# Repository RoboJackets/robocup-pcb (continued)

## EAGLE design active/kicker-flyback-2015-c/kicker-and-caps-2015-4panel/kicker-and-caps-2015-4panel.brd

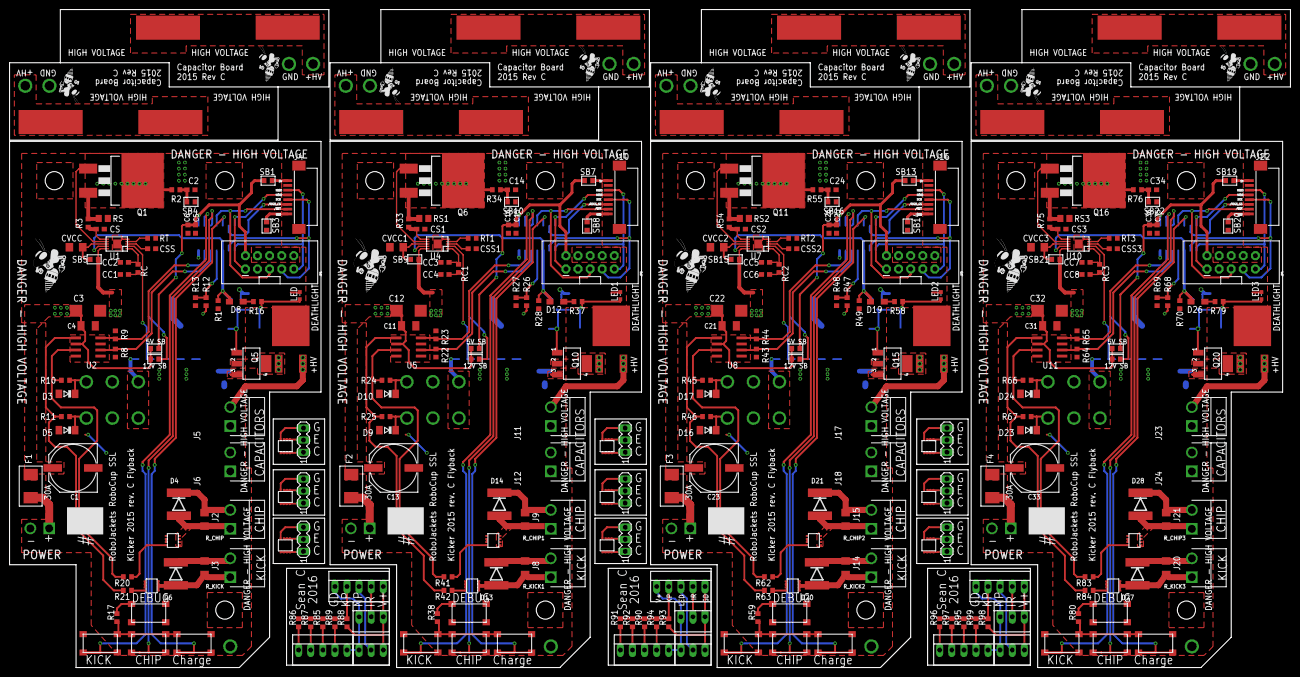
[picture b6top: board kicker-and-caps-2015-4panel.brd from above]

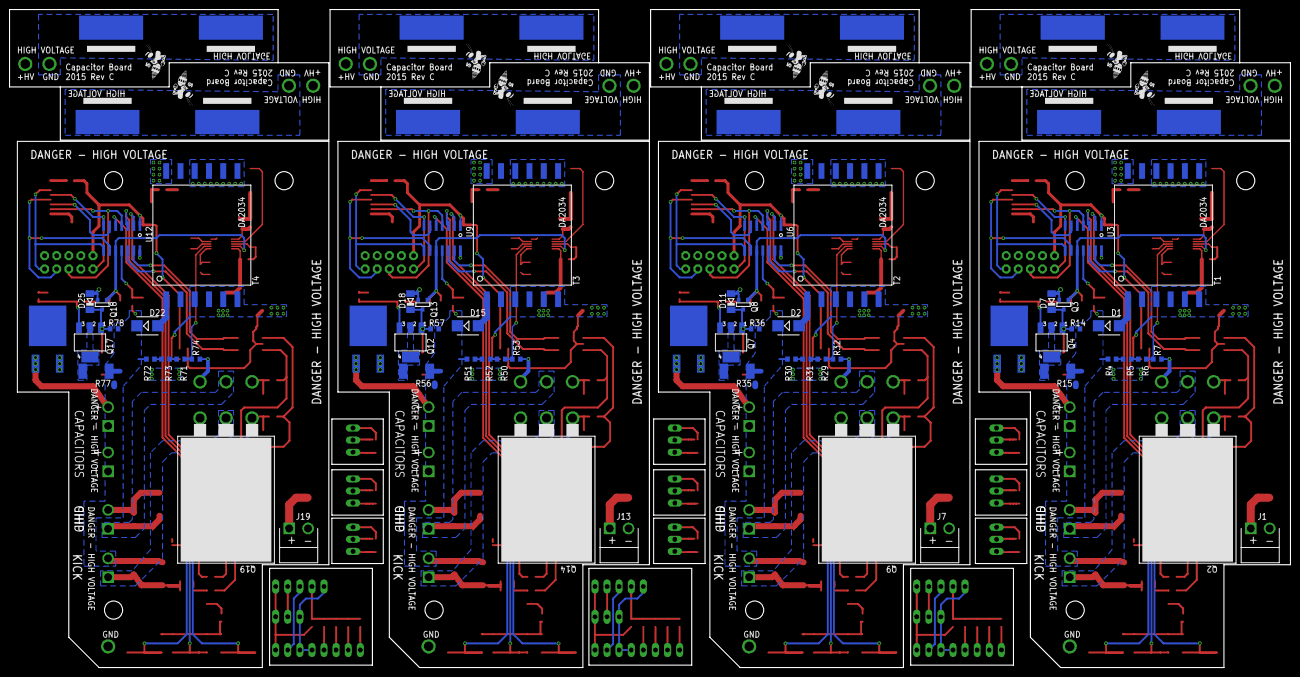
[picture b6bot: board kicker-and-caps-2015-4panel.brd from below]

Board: 2 copper layers, 269.0 x 138.2 mm, 397 parts (68 on the bottom side), 266 nets.

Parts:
C1, C13, C23, C33: UWT1E471MNL1GS; PANASONIC_G
C2, C14, C24, C34: 220pF 100V; C0603
C3, C12, C22, C32: 47uF; C/6032-28R
C4, C11, C21, C31: 4.7uF; C1206K
C5, C15, C25, C35: 47u; C0603K
C6, C16, C26, C36: 4.7u; C0603K
C7, C8, C9, C10, C17, C18, C19, C20, C27, C28, C29, C30, C37, C38, C39, C40: 25MM-DIA_HORIZ
CC1, CC4, CC6, CC8: 22nF; C0603
CC2, CC3, CC5, CC7: 100pF; C0603
CS, CS1, CS2, CS3: 22nF; C0603
CSS, CSS1, CSS2, CSS3: 100nF; C0603
CVCC, CVCC1, CVCC2, CVCC3: 4.7uF, 25v; C1206
D1, D2, D15, D22: STTH3R06U; SMB
D3, D5, D7, D9, D10, D11, D16, D17, D18, D23, D24, D25: BZV55-B18,115; SOD80C
D4, D6, D13, D14, D20, D21, D27, D28: DO-214AB
D8, D12, D19, D26: BAS16H; SOD323-W
F1, F2, F3, F4: 30A; NANO2_157
J1, J7, J13, J19: POWER; JST_VH_2_RA
J2, J9, J15, J21: CHIP; JST_VH_2_RA
J3, J8, J14, J20: KICK; JST_VH_2_RA
J4, J10, J16, J22: 0528520870
J5, J11, J17, J23: Cap 1; JST_VH_2_RA
J6, J12, J18, J24: Cap 2; JST_VH_2_RA
JP1, JP2, JP3, JP4: M05X2SHD_LOCK; 2X5-SHROUDED_LOCK
LED, LED1, LED2, LED3: LTST-S270KRKT; CHIPLED_0603
Q1, Q6, Q11, Q16: STB40NF20; D2PACK
Q2, Q9, Q14, Q19: TO264_2
Q3, Q8, Q13, Q18: FDV303N; SOT-23
Q4, Q5, Q7, Q10, Q12, Q15, Q17, Q20: FQT1N80; SOT223
R1, R8, R9, R22, R23, R28, R43, R44, R49, R64, R65, R70: 10.0k; R0603
R2, R3, R33, R34, R54, R55, R75, R76: 22; R0603
R4, R5, R30, R31, R51, R52, R72, R73: 1.00M, 1% (MCR03EZPFX1004); R0603
R6, R29, R50, R71: 470k 1%; R0603
R7, R32, R53, R74: 16.20k, 1% (MCR03EZPFX1622); R0603
R10, R11, R24, R25, R45, R46, R66, R67: 10; R0603
R12, R26, R47, R68: 1.00M 1%; R0603
R13, R27, R48, R69: 16.2k 1%; R0603
R14, R36, R57, R78: 10M; R0603
R15, R35, R56, R77: RHC2512FT33K0; R2512
R16, R20, R21, R37, R41, R42, R58, R62, R63, R79, R83, R84: 220; R0603
R17, R38, R59, R80: 10K; R0603
R18, R19, R39, R40, R60, R61, R81, R82: PWR163S-25-3301J
R85, R86, R87, R88, R89, R90, R91, R92, R93, R94, R95, R96, R97, R98, R99: R0603
RC, RC1, RC2, RC3: 6.8k; R0603
RS, RS1, RS2, RS3: 0.015 (ERJ-6BWFR015V); R0805
RT, RT1, RT2, RT3: 140k; R0603
R_CHIP, R_CHIP1, R_CHIP2, R_CHIP3: NP; R1206
R_KICK, R_KICK1, R_KICK2, R_KICK3: NP; R1206
SB1, SB2, SB7, SB11, SB13, SB17, SB19, SB23: 5V_SEL; SB0603
SB3, SB8, SB14, SB20: GND_NC; SB0603
SB4, SB5, SB9, SB10, SB15, SB16, SB21, SB22: NO; SB0603
SB6, SB12, SB18, SB24: 12V Se; SB0603
SV1, SV2, SV3, SV4, SV5, SV6, SV7, SV8, SV9: MA03-1
T1, T2, T3, T4: DA2034
TP1, TP2, TP3, TP4: GND; VIA_2MM
U1, U4, U7, U10: LT3757; MSOP-10-MSE
U2, U5, U8, U11: IX4427N; SOIC-8
U3, U6, U9, U12: ATTINY441/841SSU/SSUR; SOIC-14
U$1, U$16, U$31, U$46: ROBOBUZZ_0.6X
U$2, U$3, U$4, U$5, U$17, U$18, U$19, U$20, U$32, U$33, U$34, U$35, U$47, U$48, U$49, U$50: PTS645SK50SMTR92
U$6, U$7, U$21, U$22, U$36, U$37, U$51, U$52, U$61, U$62, U$63, U$64, U$65, U$66, U$67, U$68, U$69: TIG058E8-TL-H; ECH8
U$8, U$9, U$12, U$13, U$23, U$24, U$27, U$28, U$38, U$39, U$42, U$43, U$53, U$54, U$57, U$58: VIA_2MM
U$10, U$11, U$14, U$15, U$25, U$26, U$29, U$30, U$40, U$41, U$44, U$45, U$55, U$56, U$59, U$60: ROBOBUZZ_0.4X
X1, X2, X5, X6, X9, X10: 22-23-2031
X3, X4, X7, X8, X11, X12: 22-23-2051

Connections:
5V: J4.8, SB1.1
5V1: J10.8, SB7.1
5V2: J16.8, SB13.1
5V3: J22.8, SB19.1
+12V: C1.+, F1.P$2, SB5.1, SB6.2, T1.3, T1.4, T1.5, T1.6, U1.10
+12V1: C13.+, F2.P$2, SB9.1, SB12.2, T2.3, T2.4, T2.5, T2.6, U4.10
+12V2: C23.+, F3.P$2, SB15.1, SB18.2, T3.3, T3.4, T3.5, T3.6, U7.10
+12V3: C33.+, F4.P$2, SB21.1, SB24.2, T4.3, T4.4, T4.5, T4.6, U10.10
/KICK_CS: J4.3, U3.6
/KICK_CS1: J10.3, U6.6
/KICK_CS2: J16.3, U9.6
/KICK_CS3: J22.3, U12.6
/RST: J4.2, JP1.5, U3.4
/RST1: J10.2, JP2.5, U6.4
/RST2: J16.2, JP3.5, U9.4
/RST3: J22.2, JP4.5, U12.4
C: SV1.1, U$61.P5, U$61.P6, U$61.P7, U$61.P8
C1: SV2.1, U$62.P5, U$62.P6, U$62.P7, U$62.P8
C2: SV3.1, U$63.P5, U$63.P6, U$63.P7, U$63.P8
C3: SV4.1, U$64.P5, U$64.P6, U$64.P7, U$64.P8
C4: SV5.1, U$65.P5, U$65.P6, U$65.P7, U$65.P8
C5: SV6.1, U$66.P5, U$66.P6, U$66.P7, U$66.P8
C6: SV7.1, U$67.P5, U$67.P6, U$67.P7, U$67.P8
C7: SV8.1, U$68.P5, U$68.P6, U$68.P7, U$68.P8
C8: SV9.1, U$69.P5, U$69.P6, U$69.P7, U$69.P8
CHARGE: D8.A, Q3.3, R1.2, U1.9, U3.10
CHARGE1: D12.A, Q8.3, R28.2, U4.9, U6.10
CHARGE2: D19.A, Q13.3, R49.2, U7.9, U9.10
CHARGE3: D26.A, Q18.3, R70.2, U10.9, U12.10
CHIP: R8.2, U2.2, U3.12
CHIP1: R22.2, U5.2, U6.12
CHIP2: R43.2, U8.2, U9.12
CHIP3: R64.2, U11.2, U12.12
DB_CHG: U3.5, U$4.1, U$4.2
DB_CHG1: U6.5, U$19.1, U$19.2
DB_CHG2: U9.5, U$34.1, U$34.2
DB_CHG3: U12.5, U$49.1, U$49.2
DB_CHIP: U3.3, U$3.1, U$3.2
DB_CHIP1: U6.3, U$18.1, U$18.2
DB_CHIP2: U9.3, U$33.1, U$33.2
DB_CHIP3: U12.3, U$48.1, U$48.2
DB_KICK: U3.2, U$5.1, U$5.2
DB_KICK1: U6.2, U$20.1, U$20.2
DB_KICK2: U9.2, U$35.1, U$35.2
DB_KICK3: U12.2, U$50.1, U$50.2
E: SV1.2, U$61.P1, U$61.P2, U$61.P3
E1: SV2.2, U$62.P1, U$62.P2, U$62.P3
E2: SV3.2, U$63.P1, U$63.P2, U$63.P3
E3: SV4.2, U$64.P1, U$64.P2, U$64.P3
E4: SV5.2, U$65.P1, U$65.P2, U$65.P3
E5: SV6.2, U$66.P1, U$66.P2, U$66.P3
E6: SV7.2, U$67.P1, U$67.P2, U$67.P3
E7: SV8.2, U$68.P1, U$68.P2, U$68.P3
E8: SV9.2, U$69.P1, U$69.P2, U$69.P3
G: SV1.3, U$61.P4
G1: SV2.3, U$62.P4
G2: SV3.3, U$63.P4
G3: SV4.3, U$64.P4
G4: SV5.3, U$65.P4
G5: SV6.3, U$66.P4
G6: SV7.3, U$67.P4
G7: SV8.3, U$68.P4
G8: SV9.3, U$69.P4
GATE_C: R20.1, U$6.P4
GATE_C1: R41.1, U$21.P4
GATE_C2: R62.1, U$36.P4
GATE_C3: R83.1, U$51.P4
GATE_K: R21.1, U$7.P4
GATE_K1: R42.1, U$22.P4
GATE_K2: R63.1, U$37.P4
GATE_K3: R84.1, U$52.P4
GND: C1.-, C2.2, C3.-, C4.2, C5.2, C6.2, CC1.2, CC2.2, CS.2, CSS.2, CVCC.2, D3.A, D5.A, D7.A, J1.2, J5.1, J6.1, JP1.4, JP1.6, JP1.8, JP1.10, LED.C, Q2.E_BOT, Q2.E_TOP, Q3.2, Q5.3, R1.1, R7.1, R8.1, R9.1, R13.1, RS.1, RT.2, SB3.1, SB4.2, T1.12, TP1.P$1, U1.5, U1.11, U2.3, U3.14, U$2.3, U$2.4, U$6.P1, U$6.P2, U$6.P3, U$7.P1, U$7.P2, U$7.P3
GND1: C7.-, C8.-, U$9.P$1
GND2: C9.-, C10.-, U$13.P$1
GND3: C11.2, C12.-, C13.-, C14.2, C15.2, C16.2, CC3.2, CC4.2, CS1.2, CSS1.2, CVCC1.2, D9.A, D10.A, D11.A, J7.2, J11.1, J12.1, JP2.4, JP2.6, JP2.8, JP2.10, LED1.C, Q8.2, Q9.E_BOT, Q9.E_TOP, Q10.3, R22.1, R23.1, R27.1, R28.1, R32.1, RS1.1, RT1.2, SB8.1, SB10.2, T2.12, TP2.P$1, U4.5, U4.11, U5.3, U6.14, U$17.3, U$17.4, U$21.P1, U$21.P2, U$21.P3, U$22.P1, U$22.P2, U$22.P3
GND4: C17.-, C18.-, U$24.P$1
GND5: C19.-, C20.-, U$28.P$1
GND6: C21.2, C22.-, C23.-, C24.2, C25.2, C26.2, CC5.2, CC6.2, CS2.2, CSS2.2, CVCC2.2, D16.A, D17.A, D18.A, J13.2, J17.1, J18.1, JP3.4, JP3.6, JP3.8, JP3.10, LED2.C, Q13.2, Q14.E_BOT, Q14.E_TOP, Q15.3, R43.1, R44.1, R48.1, R49.1, R53.1, RS2.1, RT2.2, SB14.1, SB16.2, T3.12, TP3.P$1, U7.5, U7.11, U8.3, U9.14, U$32.3, U$32.4, U$36.P1, U$36.P2, U$36.P3, U$37.P1, U$37.P2, U$37.P3
GND7: C27.-, C28.-, U$39.P$1
GND8: C29.-, C30.-, U$43.P$1
GND9: C31.2, C32.-, C33.-, C34.2, C35.2, C36.2, CC7.2, CC8.2, CS3.2, CSS3.2, CVCC3.2, D23.A, D24.A, D25.A, J19.2, J23.1, J24.1, JP4.4, JP4.6, JP4.8, JP4.10, LED3.C, Q18.2, Q19.E_BOT, Q19.E_TOP, Q20.3, R64.1, R65.1, R69.1, R70.1, R74.1, RS3.1, RT3.2, SB20.1, SB22.2, T4.12, TP4.P$1, U10.5, U10.11, U11.3, U12.14, U$47.3, U$47.4, U$51.P1, U$51.P2, U$51.P3, U$52.P1, U$52.P2, U$52.P3
GND10: C37.-, C38.-, U$54.P$1
GND11: C39.-, C40.-, U$58.P$1
GND12: R88.1, X1.3, X2.3, X4.5
GND13: R93.1, X5.3, X6.3, X8.5
GND14: R98.1, X9.3, X10.3, X12.5
HV: D1.C, D4.C, D6.C, J2.2, J3.2, J5.2, J6.2, R4.2, R12.2, R14.2, R15.2, R18.P$3, R19.P$2, R_CHIP.2, R_KICK.2
HV1: C7.+, C8.+, U$8.P$1
HV2: C9.+, C10.+, U$12.P$1
HV3: D2.C, D13.C, D14.C, J8.2, J9.2, J11.2, J12.2, R26.2, R30.2, R35.2, R36.2, R39.P$3, R40.P$2, R_CHIP1.2, R_KICK1.2
HV4: C17.+, C18.+, U$23.P$1
HV5: C19.+, C20.+, U$27.P$1
HV6: D15.C, D20.C, D21.C, J14.2, J15.2, J17.2, J18.2, R47.2, R51.2, R56.2, R57.2, R60.P$3, R61.P$2, R_CHIP2.2, R_KICK2.2
HV7: C27.+, C28.+, U$38.P$1
HV8: C29.+, C30.+, U$42.P$1
HV9: D22.C, D27.C, D28.C, J20.2, J21.2, J23.2, J24.2, R68.2, R72.2, R77.2, R78.2, R81.P$3, R82.P$2, R_CHIP3.2, R_KICK3.2
HV10: C37.+, C38.+, U$53.P$1
HV11: C39.+, C40.+, U$57.P$1
IR: X2.2, X4.4
IR1: X6.2, X8.4
IR2: X10.2, X12.4
KEYPAD: R85.2, R86.2, R87.2, R88.2, R89.2, X4.2
KEYPAD1: R90.2, R91.2, R92.2, R93.2, R94.2, X8.2
KEYPAD2: R95.2, R96.2, R97.2, R98.2, R99.2, X12.2
KICK: R9.2, U2.4, U3.13
KICK1: R23.2, U5.4, U6.13
KICK2: R44.2, U8.4, U9.13
KICK3: R65.2, U11.4, U12.13
LED: X1.2, X4.3
LED1: X5.2, X8.3
LED2: X9.2, X12.3
MISO: J4.6, JP1.9, U3.8
MISO1: J10.6, JP2.9, U6.8
MISO2: J16.6, JP3.9, U9.8
MISO3: J22.6, JP4.9, U12.8
MOSI: J4.5, JP1.1, U3.7
MOSI1: J10.5, JP2.1, U6.7
MOSI2: J16.5, JP3.1, U9.7
MOSI3: J22.5, JP4.1, U12.7
unnamed: D3.C, Q2.G_TOP, R10.2
unnamed: Q1.1, U1.7
unnamed: J4.1, SB3.2
unnamed: CC2.1, RC.1, U1.1
unnamed: CC1.1, RC.2
unnamed: R11.1, R21.2, U2.5
unnamed: R4.1, R5.2
unnamed: D5.C, Q2.G_BOT, R11.2
unnamed: R5.1, R6.2
unnamed: D6.A, J3.1, Q2.C_BOT, R_KICK.1, U$7.P5, U$7.P6, U$7.P7, U$7.P8
unnamed: D4.A, J2.1, Q2.C_TOP, R_CHIP.1, U$6.P5, U$6.P6, U$6.P7, U$6.P8
unnamed: R17.2, U$2.1, U$2.2
unnamed: Q6.1, U4.7
unnamed: C3.+, C4.1, SB2.1, SB6.1, U2.6
unnamed: R10.1, R20.2, U2.7
unnamed: R17.1, U$3.3, U$3.4, U$4.3, U$4.4, U$5.3, U$5.4
unnamed: F2.P$1, J7.1
unnamed: R24.1, R41.2, U5.7
unnamed: Q5.2, Q5.4, R18.P$2, R19.P$3
unnamed: D7.C, Q3.1, Q4.1, Q5.1, R14.1
unnamed: Q4.2, Q4.4, R15.1
unnamed: D9.C, Q9.G_BOT, R25.2
unnamed: CC3.1, RC1.1, U4.1
unnamed: F1.P$1, J1.1
unnamed: CSS1.1, U4.3
unnamed: CSS.1, U1.3
unnamed: RT.1, U1.4
unnamed: CVCC.1, SB5.2, U1.8
unnamed: LED.A, Q4.3, R16.2
unnamed: CS.1, R3.1, U1.6
unnamed: C2.1, R2.1, SB4.1
unnamed: D8.C, R16.1
unnamed: RT1.1, U4.4
unnamed: CC4.1, RC1.2
unnamed: CVCC1.1, SB9.2, U4.8
unnamed: J10.1, SB8.2
unnamed: CS1.1, R33.1, U4.6
unnamed: C14.1, R34.1, SB10.1
unnamed: D11.C, Q7.1, Q8.1, Q10.1, R36.1
unnamed: LED1.A, Q7.3, R37.2
unnamed: D12.C, R37.1
unnamed: Q7.2, Q7.4, R35.1
unnamed: D14.A, J9.1, Q9.C_TOP, R_CHIP1.1, U$21.P5, U$21.P6, U$21.P7, U$21.P8
unnamed: D10.C, Q9.G_TOP, R24.2
unnamed: Q1.2, R2.2, T1.7, T1.8, T1.9, T1.10
unnamed: Q6.2, R34.2, T2.7, T2.8, T2.9, T2.10
unnamed: D2.A, T2.1
unnamed: D1.A, T1.1
unnamed: R25.1, R42.2, U5.5
unnamed: D13.A, J8.1, Q9.C_BOT, R_KICK1.1, U$22.P5, U$22.P6, U$22.P7, U$22.P8
unnamed: R30.1, R31.2
unnamed: R29.2, R31.1
unnamed: R38.1, U$18.3, U$18.4, U$19.3, U$19.4, U$20.3, U$20.4
unnamed: R38.2, U$17.1, U$17.2
unnamed: Q10.2, Q10.4, R39.P$2, R40.P$3
unnamed: C11.1, C12.+, SB11.1, SB12.1, U5.6
unnamed: Q11.1, U7.7
unnamed: F3.P$1, J13.1
unnamed: R45.1, R62.2, U8.7
unnamed: D16.C, Q14.G_BOT, R46.2
unnamed: CC5.1, RC2.1, U7.1
unnamed: CSS2.1, U7.3
unnamed: RT2.1, U7.4
unnamed: CC6.1, RC2.2
unnamed: CVCC2.1, SB15.2, U7.8
unnamed: J16.1, SB14.2
unnamed: CS2.1, R54.1, U7.6
unnamed: C24.1, R55.1, SB16.1
unnamed: D18.C, Q12.1, Q13.1, Q15.1, R57.1
unnamed: LED2.A, Q12.3, R58.2
unnamed: D19.C, R58.1
unnamed: Q12.2, Q12.4, R56.1
unnamed: D21.A, J15.1, Q14.C_TOP, R_CHIP2.1, U$36.P5, U$36.P6, U$36.P7, U$36.P8
unnamed: D17.C, Q14.G_TOP, R45.2
unnamed: Q11.2, R55.2, T3.7, T3.8, T3.9, T3.10
unnamed: D15.A, T3.1
unnamed: R46.1, R63.2, U8.5
unnamed: D20.A, J14.1, Q14.C_BOT, R_KICK2.1, U$37.P5, U$37.P6, U$37.P7, U$37.P8
unnamed: R51.1, R52.2
unnamed: R50.2, R52.1
unnamed: R59.1, U$33.3, U$33.4, U$34.3, U$34.4, U$35.3, U$35.4
unnamed: R59.2, U$32.1, U$32.2
unnamed: Q15.2, Q15.4, R60.P$2, R61.P$3
unnamed: C21.1, C22.+, SB17.1, SB18.1, U8.6
unnamed: Q16.1, U10.7
unnamed: F4.P$1, J19.1
unnamed: R66.1, R83.2, U11.7
unnamed: D23.C, Q19.G_BOT, R67.2
unnamed: CC7.1, RC3.1, U10.1
unnamed: CSS3.1, U10.3
unnamed: RT3.1, U10.4
unnamed: CC8.1, RC3.2
unnamed: CVCC3.1, SB21.2, U10.8
unnamed: J22.1, SB20.2
unnamed: CS3.1, R75.1, U10.6
unnamed: C34.1, R76.1, SB22.1
unnamed: D25.C, Q17.1, Q18.1, Q20.1, R78.1
unnamed: LED3.A, Q17.3, R79.2
unnamed: D26.C, R79.1
unnamed: Q17.2, Q17.4, R77.1
unnamed: D28.A, J21.1, Q19.C_TOP, R_CHIP3.1, U$51.P5, U$51.P6, U$51.P7, U$51.P8
unnamed: D24.C, Q19.G_TOP, R66.2
unnamed: Q16.2, R76.2, T4.7, T4.8, T4.9, T4.10
unnamed: D22.A, T4.1
unnamed: R67.1, R84.2, U11.5
unnamed: D27.A, J20.1, Q19.C_BOT, R_KICK3.1, U$52.P5, U$52.P6, U$52.P7, U$52.P8
unnamed: R72.1, R73.2
unnamed: R71.2, R73.1
unnamed: R80.1, U$48.3, U$48.4, U$49.3, U$49.4, U$50.3, U$50.4
unnamed: R80.2, U$47.1, U$47.2
unnamed: Q20.2, Q20.4, R81.P$2, R82.P$3
unnamed: C31.1, C32.+, SB23.1, SB24.1, U11.6
unnamed: R89.1, X3.4
unnamed: R85.1, X3.3
unnamed: R87.1, X3.2
unnamed: R86.1, X3.1
unnamed: R94.1, X7.4
unnamed: R90.1, X7.3
unnamed: R92.1, X7.2
unnamed: R91.1, X7.1
unnamed: R99.1, X11.4
unnamed: R95.1, X11.3
unnamed: R97.1, X11.2
unnamed: R96.1, X11.1
NAG: Q1.3, R3.2, RS.2
NAG1: Q6.3, R33.2, RS1.2
NAG2: Q11.3, R54.2, RS2.2
NAG3: Q16.3, R75.2, RS3.2
SCK: J4.4, JP1.7, U3.9
SCK1: J10.4, JP2.7, U6.9
SCK2: J16.4, JP3.7, U9.9
SCK3: J22.4, JP4.7, U12.9
VCC: X1.1, X2.1, X3.5, X4.1
VCC1: X5.1, X6.1, X7.5, X8.1
VCC2: X9.1, X10.1, X11.5, X12.1
VDD: C5.1, C6.1, JP1.2, SB1.2, SB2.2, U3.1
VDD1: C15.1, C16.1, JP2.2, SB7.2, SB11.2, U6.1
VDD2: C25.1, C26.1, JP3.2, SB13.2, SB17.2, U9.1
VDD3: C35.1, C36.1, JP4.2, SB19.2, SB23.2, U12.1
VFB: R6.1, R7.2, U1.2
VFB1: R29.1, R32.2, U4.2
VFB2: R50.1, R53.2, U7.2
VFB3: R71.1, R74.2, U10.2
V_MONITOR: R12.1, R13.2, U3.11
V_MONITOR1: R26.1, R27.2, U6.11
V_MONITOR2: R47.1, R48.2, U9.11
V_MONITOR3: R68.1, R69.2, U12.11

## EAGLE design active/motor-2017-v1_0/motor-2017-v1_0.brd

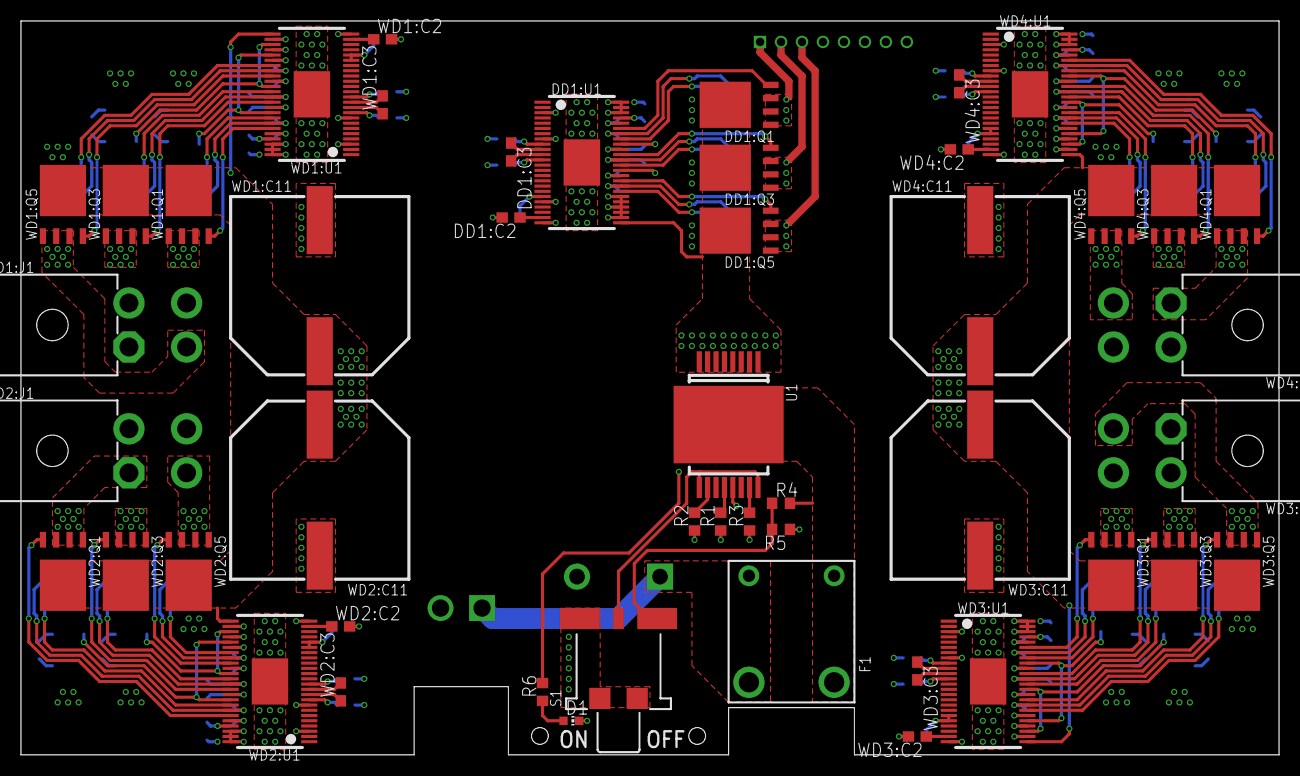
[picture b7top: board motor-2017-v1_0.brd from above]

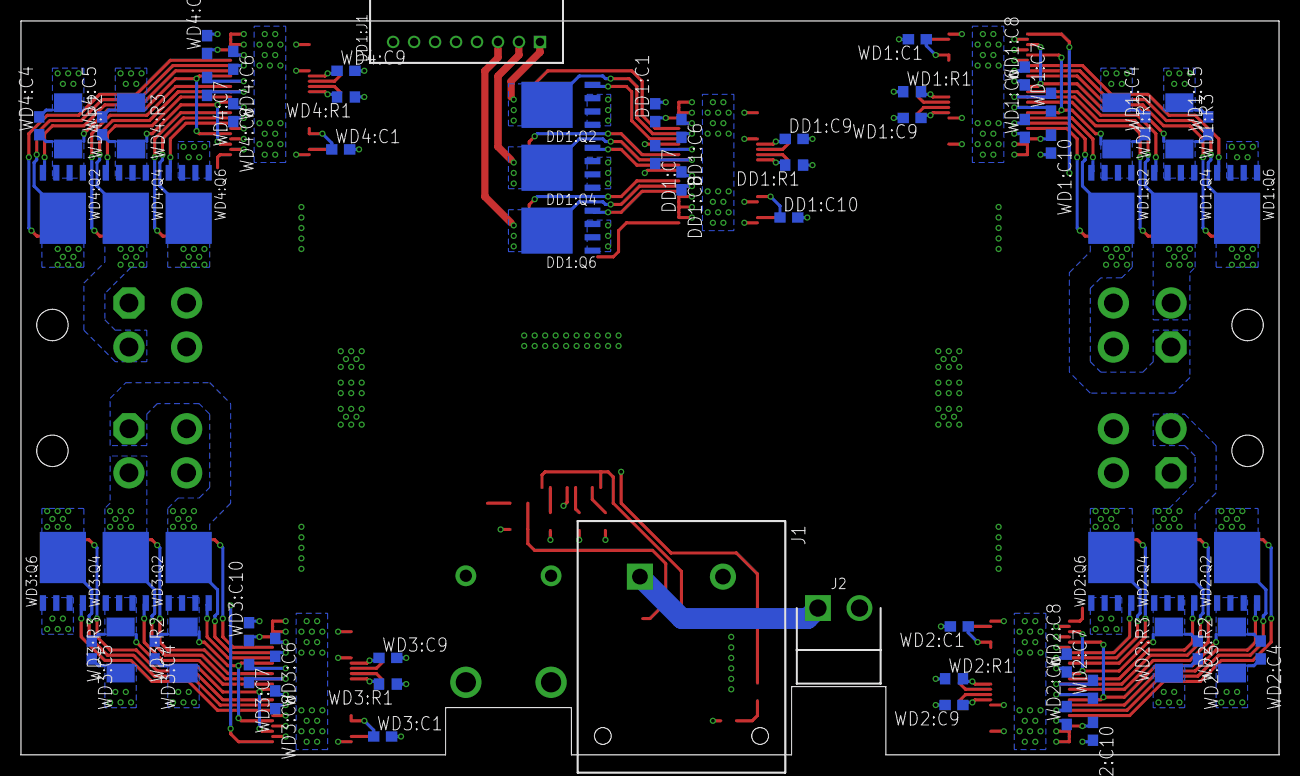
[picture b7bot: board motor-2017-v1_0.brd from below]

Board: 4 copper layers, 120.0 x 70.0 mm, 117 parts (69 on the bottom side), 104 nets.

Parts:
D1: Green; CHIP-LED0603
DD1:C1, DD1:C2: 1uF; C0603
DD1:C3: 22000pF 50V; C0603
DD1:C6, DD1:C7, DD1:C8, DD1:C10: 0.1uF 50V; C0603
DD1:C9: 2.2uF 50V; C0603
DD1:J1: 8-PIN_2MM-H; 2MM-8-H
DD1:Q1, DD1:Q2, DD1:Q3, DD1:Q4, DD1:Q5, DD1:Q6: IRFH7545; PQFN_5X6_E
DD1:R1: 10k; R0603
DD1:U1: DRV8303DCA; TSSOP-48_PAD
F1: 30A; FUSEHOLDER_3549_X2
J1: DF22-2; DF22-2-H
J2: B2PS-CENTERED-VH(LF)(SN); B2PS-CENTERED
R1: 10k; R0603
R2, R3, R6: 1k; R0603
R4: 270k; R0603
R5: 100k; R0603
S1: 34EWMSP12MRT; 34EWMSP12M6RT
U1: VND5E006ASPTR-E; POWERSO-16
WD1:C1, WD1:C2, WD2:C1, WD2:C2, WD3:C1, WD3:C2, WD4:C1, WD4:C2: 1uF; C0603
WD1:C3, WD2:C3, WD3:C3, WD4:C3: 22000pF 50V; C0603
WD1:C4, WD1:C5, WD2:C4, WD2:C5, WD3:C4, WD3:C5, WD4:C4, WD4:C5: 10000pF 50V; C0603
WD1:C6, WD1:C7, WD1:C8, WD1:C10, WD2:C6, WD2:C7, WD2:C8, WD2:C10, WD3:C6, WD3:C7, WD3:C8, WD3:C10, WD4:C6, WD4:C7, WD4:C8, WD4:C10: 0.1uF 50V; C0603
WD1:C9, WD2:C9, WD3:C9, WD4:C9: 2.2uF 50V; C0603
WD1:C11, WD2:C11, WD3:C11, WD4:C11: EEE-FK1H102AM; PANASONIC_J16
WD1:J1, WD2:J1, WD3:J1, WD4:J1: MINIFITJR_HDR_2X2; 0039301040
WD1:Q1, WD1:Q2, WD1:Q3, WD1:Q4, WD1:Q5, WD1:Q6, WD2:Q1, WD2:Q2, WD2:Q3, WD2:Q4, WD2:Q5, WD2:Q6, WD3:Q1, WD3:Q2, WD3:Q3, WD3:Q4, WD3:Q5, WD3:Q6, WD4:Q1, WD4:Q2, WD4:Q3, WD4:Q4, WD4:Q5, WD4:Q6: IRFH7545; PQFN_5X6_E
WD1:R1, WD2:R1, WD3:R1, WD4:R1: 10k; R0603
WD1:R2, WD1:R3, WD2:R2, WD2:R3, WD3:R2, WD3:R3, WD4:R2, WD4:R3: ERJ-MB1SF1M0U; R2010
WD1:U1, WD2:U1, WD3:U1, WD4:U1: DRV8303DCA; TSSOP-48_PAD

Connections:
+3.3V: DD1:C1.1, DD1:C10.1, DD1:J1.7, DD1:R1.1, DD1:U1.19, DD1:U1.45, WD1:C1.1, WD1:C10.1, WD1:R1.1, WD1:U1.19, WD1:U1.20, WD1:U1.45, WD2:C1.1, WD2:C10.1, WD2:R1.1, WD2:U1.19, WD2:U1.20, WD2:U1.45, WD3:C1.1, WD3:C10.1, WD3:R1.1, WD3:U1.19, WD3:U1.20, WD3:U1.45, WD4:C1.1, WD4:C10.1, WD4:R1.1, WD4:U1.19, WD4:U1.20, WD4:U1.45
+18.5V: DD1:Q1.5678, DD1:Q3.5678, DD1:Q5.5678, DD1:U1.25, R6.2, U1.1, U1.2, U1.3, U1.4, U1.5, U1.6, U1.7, U1.8, WD1:C11.+, WD1:Q1.5678, WD1:Q3.5678, WD1:Q5.5678, WD1:U1.25, WD2:C11.+, WD2:Q1.5678, WD2:Q3.5678, WD2:Q5.5678, WD2:U1.25, WD3:C11.+, WD3:Q1.5678, WD3:Q3.5678, WD3:Q5.5678, WD3:U1.25, WD4:C11.+, WD4:Q1.5678, WD4:Q3.5678, WD4:Q5.5678, WD4:U1.25
DD1:N$1: DD1:C2.1, DD1:U1.23
DD1:N$2: DD1:C3.1, DD1:U1.10
DD1:N$3: DD1:C3.2, DD1:U1.11
DD1:N$4: DD1:C9.1, DD1:U1.9
DD1:N$6: DD1:Q2.4, DD1:U1.41
DD1:N$8: DD1:Q1.4, DD1:U1.43
DD1:N$10: DD1:Q4.4, DD1:U1.36
DD1:N$12: DD1:Q3.4, DD1:U1.38
DD1:N$13: DD1:C6.1, DD1:U1.44
DD1:N$14: DD1:C7.1, DD1:U1.39
DD1:N$16: DD1:Q6.4, DD1:U1.31
DD1:N$17: DD1:Q5.4, DD1:U1.33
DD1:N$18: DD1:C8.1, DD1:U1.34
DD1:N$19: DD1:R1.2, DD1:U1.12
DD1:PHASE_A: DD1:C6.2, DD1:J1.1, DD1:Q1.1, DD1:Q1.2, DD1:Q1.3, DD1:Q2.5678, DD1:U1.42
DD1:PHASE_B: DD1:C7.2, DD1:J1.2, DD1:Q3.1, DD1:Q3.2, DD1:Q3.3, DD1:Q4.5678, DD1:U1.37
DD1:PHASE_C: DD1:C8.2, DD1:J1.3, DD1:Q5.1, DD1:Q5.2, DD1:Q5.3, DD1:Q6.5678, DD1:U1.32
GND: D1.C, DD1:C1.2, DD1:C2.2, DD1:C9.2, DD1:C10.2, DD1:J1.8, DD1:Q2.1, DD1:Q2.2, DD1:Q2.3, DD1:Q4.1, DD1:Q4.2, DD1:Q4.3, DD1:Q6.1, DD1:Q6.2, DD1:Q6.3, DD1:U1.3, DD1:U1.8, DD1:U1.20, DD1:U1.24, DD1:U1.26, DD1:U1.27, DD1:U1.28, DD1:U1.29, DD1:U1.30, DD1:U1.35, DD1:U1.40, DD1:U1.46, DD1:U1.47, DD1:U1.48, DD1:U1.PAD, J1.2, J2.2, R1.1, R2.1, R3.1, R5.1, S1.3, S1.LEG1, S1.LEG3, U1.13, WD1:C1.2, WD1:C2.2, WD1:C4.2, WD1:C5.2, WD1:C9.2, WD1:C10.2, WD1:C11.-, WD1:Q6.1, WD1:Q6.2, WD1:Q6.3, WD1:R2.1, WD1:R3.1, WD1:U1.3, WD1:U1.8, WD1:U1.24, WD1:U1.26, WD1:U1.28, WD1:U1.30, WD1:U1.46, WD1:U1.47, WD1:U1.48, WD1:U1.PAD, WD2:C1.2, WD2:C2.2, WD2:C4.2, WD2:C5.2, WD2:C9.2, WD2:C10.2, WD2:C11.-, WD2:Q6.1, WD2:Q6.2, WD2:Q6.3, WD2:R2.1, WD2:R3.1, WD2:U1.3, WD2:U1.8, WD2:U1.24, WD2:U1.26, WD2:U1.28, WD2:U1.30, WD2:U1.46, WD2:U1.47, WD2:U1.48, WD2:U1.PAD, WD3:C1.2, WD3:C2.2, WD3:C4.2, WD3:C5.2, WD3:C9.2, WD3:C10.2, WD3:C11.-, WD3:Q6.1, WD3:Q6.2, WD3:Q6.3, WD3:R2.1, WD3:R3.1, WD3:U1.3, WD3:U1.8, WD3:U1.24, WD3:U1.26, WD3:U1.28, WD3:U1.30, WD3:U1.46, WD3:U1.47, WD3:U1.48, WD3:U1.PAD, WD4:C1.2, WD4:C2.2, WD4:C4.2, WD4:C5.2, WD4:C9.2, WD4:C10.2, WD4:C11.-, WD4:Q6.1, WD4:Q6.2, WD4:Q6.3, WD4:R2.1, WD4:R3.1, WD4:U1.3, WD4:U1.8, WD4:U1.24, WD4:U1.26, WD4:U1.28, WD4:U1.30, WD4:U1.46, WD4:U1.47, WD4:U1.48, WD4:U1.PAD
unnamed: R3.2, U1.15
unnamed: R2.2, U1.10
unnamed: R1.2, U1.12
unnamed: R4.1, R5.2, S1.1
unnamed: S1.2, U1.9, U1.16
unnamed: D1.A, R6.1
VBATT: F1.2, F1.LEG2, R4.2, U1.17
VIN: F1.1, F1.LEG1, J1.1, J2.1
WD1:N$1: WD1:C2.1, WD1:U1.23
WD1:N$2: WD1:C3.1, WD1:U1.10
WD1:N$3: WD1:C3.2, WD1:U1.11
WD1:N$4: WD1:C9.1, WD1:U1.9
WD1:N$6: WD1:Q2.4, WD1:U1.41
WD1:N$8: WD1:Q1.4, WD1:U1.43
WD1:N$10: WD1:Q4.4, WD1:U1.36
WD1:N$12: WD1:Q3.4, WD1:U1.38
WD1:N$13: WD1:C6.1, WD1:U1.44
WD1:N$14: WD1:C7.1, WD1:U1.39
WD1:N$16: WD1:Q6.4, WD1:U1.31
WD1:N$17: WD1:Q5.4, WD1:U1.33
WD1:N$18: WD1:C8.1, WD1:U1.34
WD1:N$19: WD1:R1.2, WD1:U1.12
WD1:PHASE_A: WD1:C6.2, WD1:J1.1, WD1:Q1.1, WD1:Q1.2, WD1:Q1.3, WD1:Q2.5678, WD1:U1.42
WD1:PHASE_B: WD1:C7.2, WD1:J1.2, WD1:Q3.1, WD1:Q3.2, WD1:Q3.3, WD1:Q4.5678, WD1:U1.37
WD1:PHASE_C: WD1:C8.2, WD1:J1.3, WD1:Q5.1, WD1:Q5.2, WD1:Q5.3, WD1:Q6.5678, WD1:U1.32
WD1:S1: WD1:C4.1, WD1:Q2.1, WD1:Q2.2, WD1:Q2.3, WD1:R2.2, WD1:U1.29, WD1:U1.40
WD1:S2: WD1:C5.1, WD1:Q4.1, WD1:Q4.2, WD1:Q4.3, WD1:R3.2, WD1:U1.27, WD1:U1.35
WD2:N$1: WD2:C2.1, WD2:U1.23
WD2:N$2: WD2:C3.1, WD2:U1.10
WD2:N$3: WD2:C3.2, WD2:U1.11
WD2:N$4: WD2:C9.1, WD2:U1.9
WD2:N$6: WD2:Q2.4, WD2:U1.41
WD2:N$8: WD2:Q1.4, WD2:U1.43
WD2:N$10: WD2:Q4.4, WD2:U1.36
WD2:N$12: WD2:Q3.4, WD2:U1.38
WD2:N$13: WD2:C6.1, WD2:U1.44
WD2:N$14: WD2:C7.1, WD2:U1.39
WD2:N$16: WD2:Q6.4, WD2:U1.31
WD2:N$17: WD2:Q5.4, WD2:U1.33
WD2:N$18: WD2:C8.1, WD2:U1.34
WD2:N$19: WD2:R1.2, WD2:U1.12
WD2:PHASE_A: WD2:C6.2, WD2:J1.1, WD2:Q1.1, WD2:Q1.2, WD2:Q1.3, WD2:Q2.5678, WD2:U1.42
WD2:PHASE_B: WD2:C7.2, WD2:J1.2, WD2:Q3.1, WD2:Q3.2, WD2:Q3.3, WD2:Q4.5678, WD2:U1.37
WD2:PHASE_C: WD2:C8.2, WD2:J1.3, WD2:Q5.1, WD2:Q5.2, WD2:Q5.3, WD2:Q6.5678, WD2:U1.32
WD2:S1: WD2:C4.1, WD2:Q2.1, WD2:Q2.2, WD2:Q2.3, WD2:R2.2, WD2:U1.29, WD2:U1.40
WD2:S2: WD2:C5.1, WD2:Q4.1, WD2:Q4.2, WD2:Q4.3, WD2:R3.2, WD2:U1.27, WD2:U1.35
WD3:N$1: WD3:C2.1, WD3:U1.23
WD3:N$2: WD3:C3.1, WD3:U1.10
WD3:N$3: WD3:C3.2, WD3:U1.11
WD3:N$4: WD3:C9.1, WD3:U1.9
WD3:N$6: WD3:Q2.4, WD3:U1.41
WD3:N$8: WD3:Q1.4, WD3:U1.43
WD3:N$10: WD3:Q4.4, WD3:U1.36
WD3:N$12: WD3:Q3.4, WD3:U1.38
WD3:N$13: WD3:C6.1, WD3:U1.44
WD3:N$14: WD3:C7.1, WD3:U1.39
WD3:N$16: WD3:Q6.4, WD3:U1.31
WD3:N$17: WD3:Q5.4, WD3:U1.33
WD3:N$18: WD3:C8.1, WD3:U1.34
WD3:N$19: WD3:R1.2, WD3:U1.12
WD3:PHASE_A: WD3:C6.2, WD3:J1.1, WD3:Q1.1, WD3:Q1.2, WD3:Q1.3, WD3:Q2.5678, WD3:U1.42
WD3:PHASE_B: WD3:C7.2, WD3:J1.2, WD3:Q3.1, WD3:Q3.2, WD3:Q3.3, WD3:Q4.5678, WD3:U1.37
WD3:PHASE_C: WD3:C8.2, WD3:J1.3, WD3:Q5.1, WD3:Q5.2, WD3:Q5.3, WD3:Q6.5678, WD3:U1.32
WD3:S1: WD3:C4.1, WD3:Q2.1, WD3:Q2.2, WD3:Q2.3, WD3:R2.2, WD3:U1.29, WD3:U1.40
WD3:S2: WD3:C5.1, WD3:Q4.1, WD3:Q4.2, WD3:Q4.3, WD3:R3.2, WD3:U1.27, WD3:U1.35
WD4:N$1: WD4:C2.1, WD4:U1.23
WD4:N$2: WD4:C3.1, WD4:U1.10
WD4:N$3: WD4:C3.2, WD4:U1.11
WD4:N$4: WD4:C9.1, WD4:U1.9
WD4:N$6: WD4:Q2.4, WD4:U1.41
WD4:N$8: WD4:Q1.4, WD4:U1.43
WD4:N$10: WD4:Q4.4, WD4:U1.36
WD4:N$12: WD4:Q3.4, WD4:U1.38
WD4:N$13: WD4:C6.1, WD4:U1.44
WD4:N$14: WD4:C7.1, WD4:U1.39
WD4:N$16: WD4:Q6.4, WD4:U1.31
WD4:N$17: WD4:Q5.4, WD4:U1.33
WD4:N$18: WD4:C8.1, WD4:U1.34
WD4:N$19: WD4:R1.2, WD4:U1.12
WD4:PHASE_A: WD4:C6.2, WD4:J1.1, WD4:Q1.1, WD4:Q1.2, WD4:Q1.3, WD4:Q2.5678, WD4:U1.42
WD4:PHASE_B: WD4:C7.2, WD4:J1.2, WD4:Q3.1, WD4:Q3.2, WD4:Q3.3, WD4:Q4.5678, WD4:U1.37
WD4:PHASE_C: WD4:C8.2, WD4:J1.3, WD4:Q5.1, WD4:Q5.2, WD4:Q5.3, WD4:Q6.5678, WD4:U1.32
WD4:S1: WD4:C4.1, WD4:Q2.1, WD4:Q2.2, WD4:Q2.3, WD4:R2.2, WD4:U1.29, WD4:U1.40
WD4:S2: WD4:C5.1, WD4:Q4.1, WD4:Q4.2, WD4:Q4.3, WD4:R3.2, WD4:U1.27, WD4:U1.35

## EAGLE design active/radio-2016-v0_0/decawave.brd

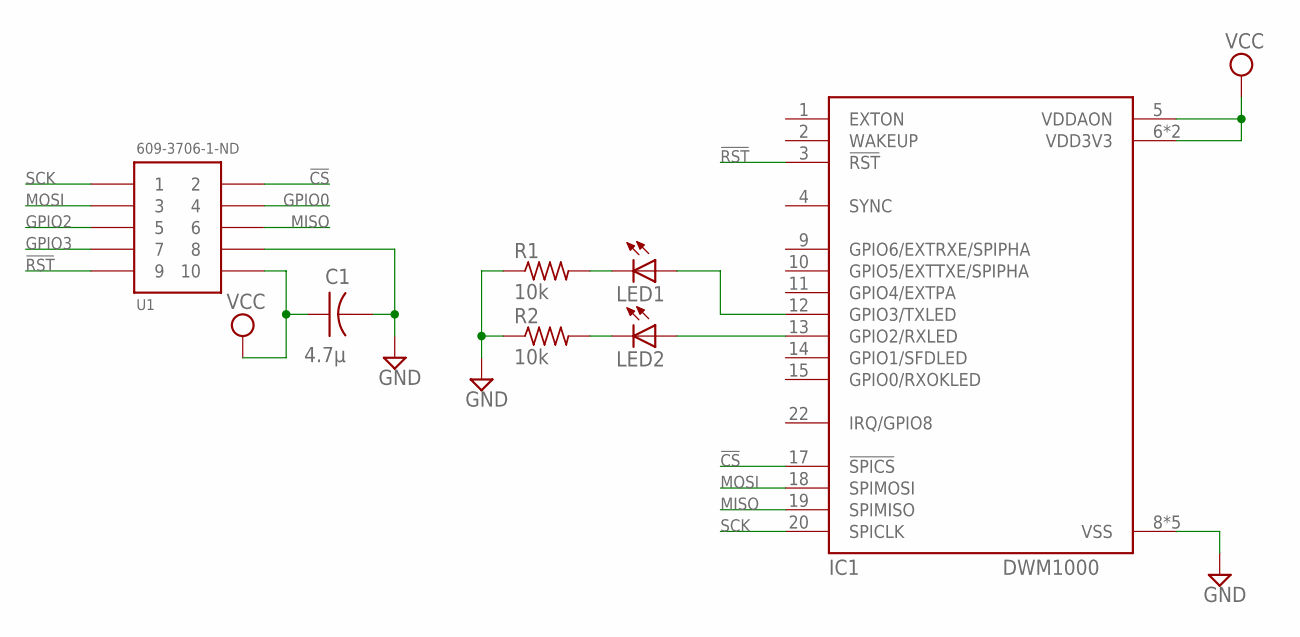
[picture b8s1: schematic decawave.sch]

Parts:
C1: 4.7µ; C0603
IC1: DWM1000
LED1, LED2: LEDCHIP-LED0805; CHIP-LED0805
R1, R2: 10k; R0603
U1: 609-3706-1-ND; 5X2_FEMALE

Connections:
!CS: IC1.17 (!SPICS), U1.2
!RST: IC1.3 (!RST), U1.9
GND: C1.2, IC1.8 (VSS), IC1.16 (VSS), IC1.21 (VSS), IC1.23 (VSS), IC1.24 (VSS), R1.1, R2.1, U1.8
GPIO0: U1.4
GPIO2: U1.5
GPIO3: U1.7
MISO: IC1.19 (SPIMISO), U1.6
MOSI: IC1.18 (SPIMOSI), U1.3
unnamed: IC1.12 (GPIO3/TXLED), LED1.A
unnamed: IC1.13 (GPIO2/RXLED), LED2.A
unnamed: LED1.C, R1.2
unnamed: LED2.C, R2.2
SCK: IC1.20 (SPICLK), U1.1
VCC: C1.1, IC1.5 (VDDAON), IC1.6 (VDD3V3), IC1.7 (VDD3V3), U1.10

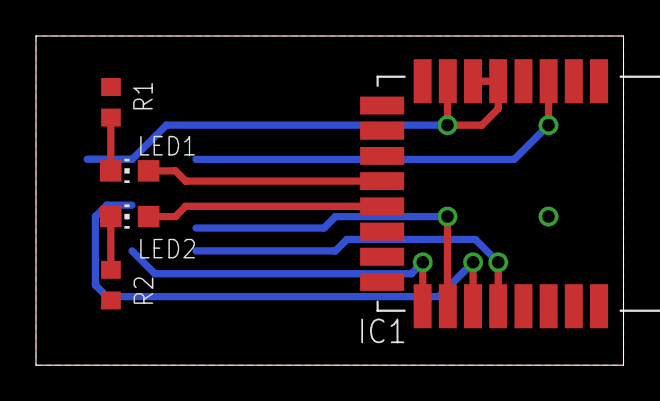
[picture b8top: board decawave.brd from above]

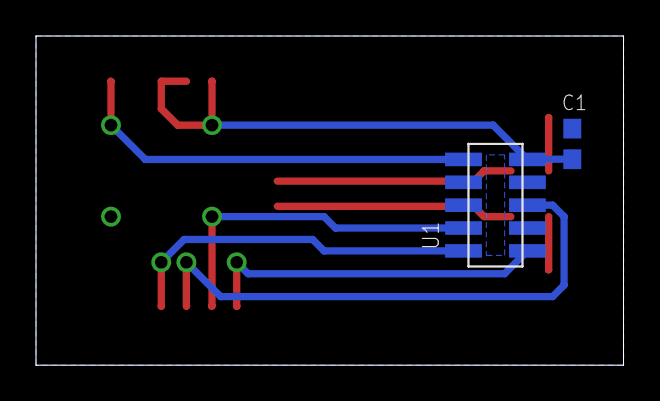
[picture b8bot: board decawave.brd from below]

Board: 2 copper layers, 32.6 x 18.3 mm, 7 parts (2 on the bottom side), 11 nets.
